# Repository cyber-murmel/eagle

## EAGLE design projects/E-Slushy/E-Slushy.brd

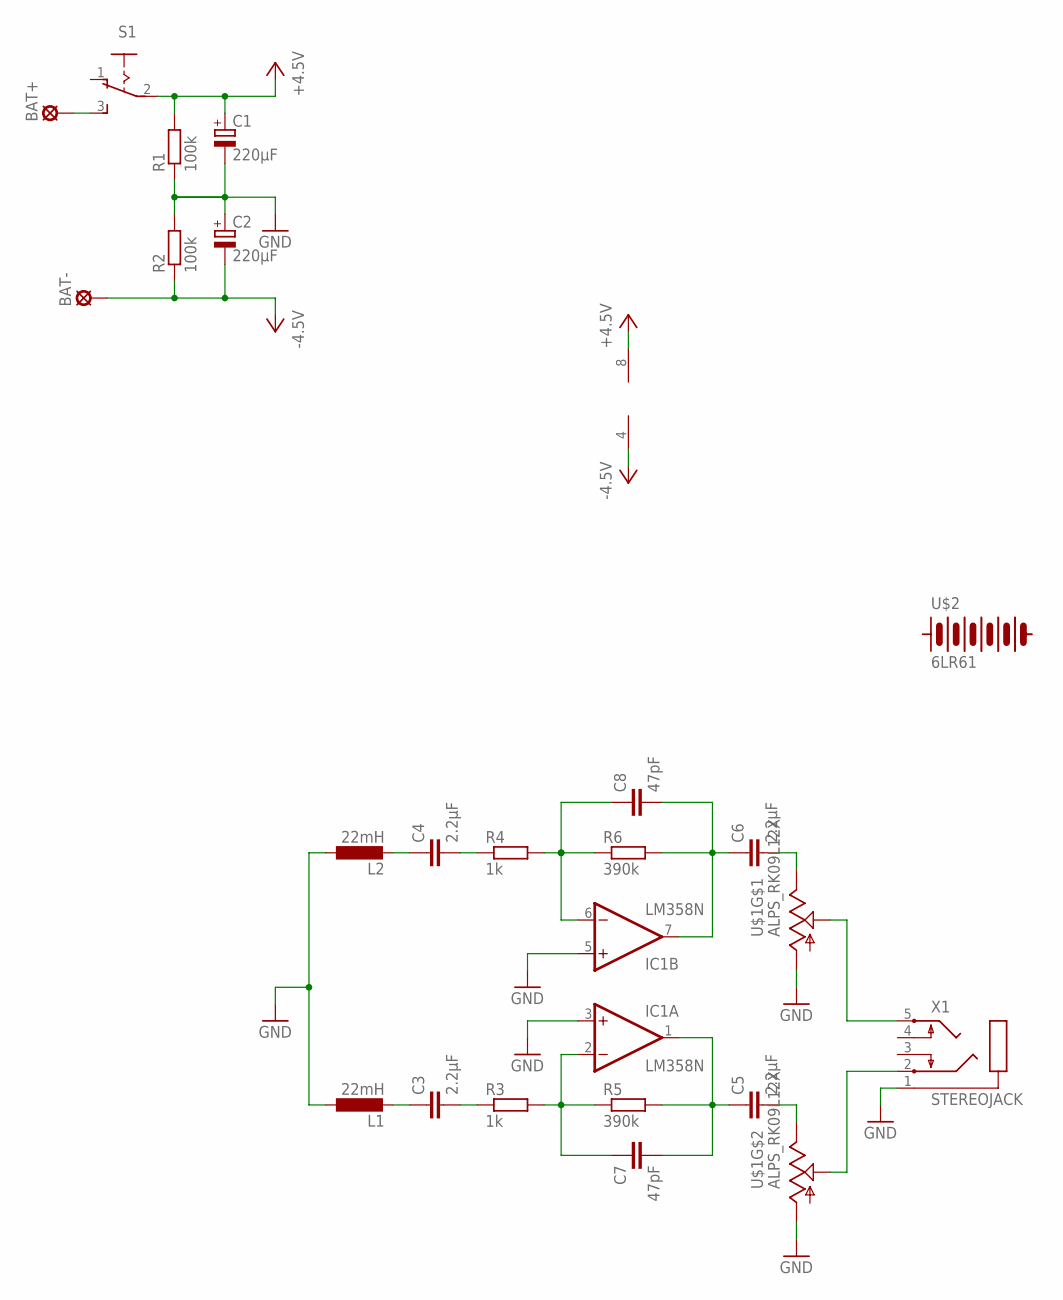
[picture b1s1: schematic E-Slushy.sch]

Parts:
BAT+: SE14
BAT-: SE14
C1, C2: 220μF; PANASONIC_D
C3, C4, C5, C6: 2.2μF; C1206K
C7, C8: 47pF; C1206K
IC1: LM358N; DIL08
L1, L2: 22mH; 6000-XXXX-RC
R1, R2: 100k; R1206
R3, R4: 1k; R1206
R5, R6: 390k; R1206
S1: 255SB
U$1: ALPS_RK09L12X; RK09L12
U$2: 6LR61
X1: STEREOJACK; STX3100

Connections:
+4.5V: C1.+, IC1.8 (V+), R1.2, S1.2
-4.5V: BAT-.MP, C2.-, IC1.4 (V-), R2.1
GND: C1.-, C2.+, IC1.3 (+IN), IC1.5 (+IN), L1.1, L2.1, R1.1, R2.2, U$1.A1 (1), U$1.B1 (1), X1.1
unnamed: C3.1, L1.2
unnamed: C3.2, R3.1
unnamed: C4.1, L2.2
unnamed: C4.2, R4.1
unnamed: C7.1, IC1.2 (-IN), R3.2, R5.1
unnamed: C5.1, C7.2, IC1.1 (OUT), R5.2
unnamed: C8.1, IC1.6 (-IN), R4.2, R6.1
unnamed: C6.1, C8.2, IC1.7 (OUT), R6.2
unnamed: C5.2, U$1.B3 (3)
unnamed: C6.2, U$1.A3 (3)
unnamed: U$1.B2 (2), X1.2
unnamed: U$1.A2 (2), X1.5
unnamed: BAT+.MP, S1.3 (S)

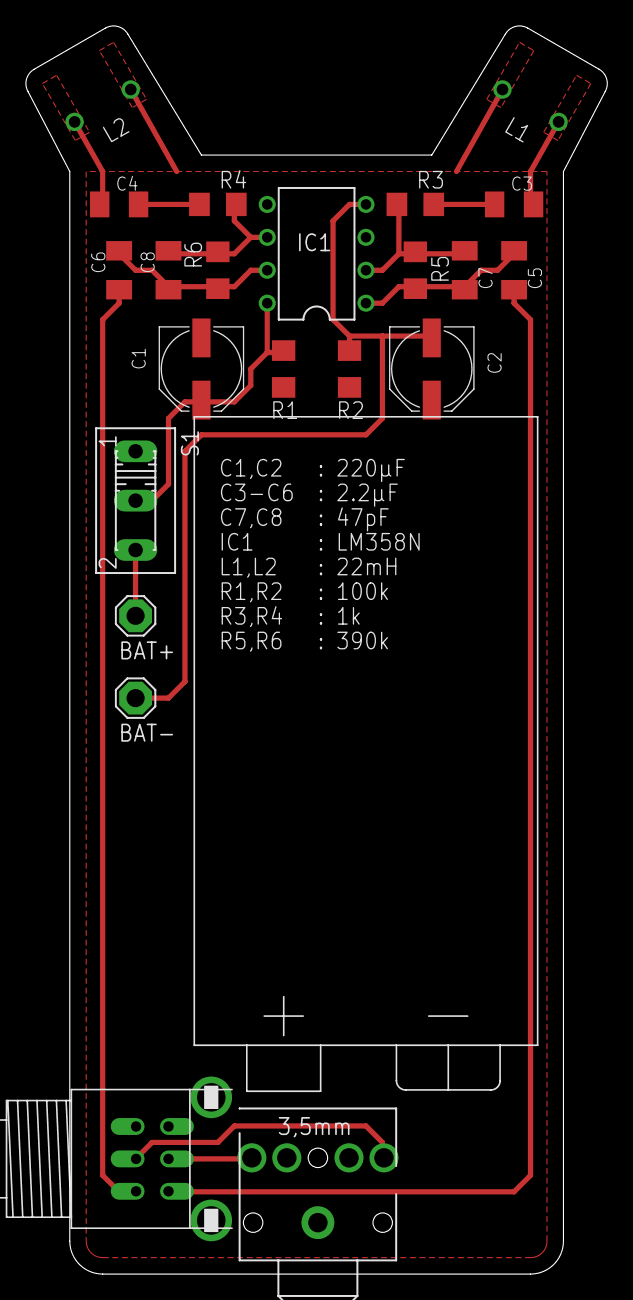
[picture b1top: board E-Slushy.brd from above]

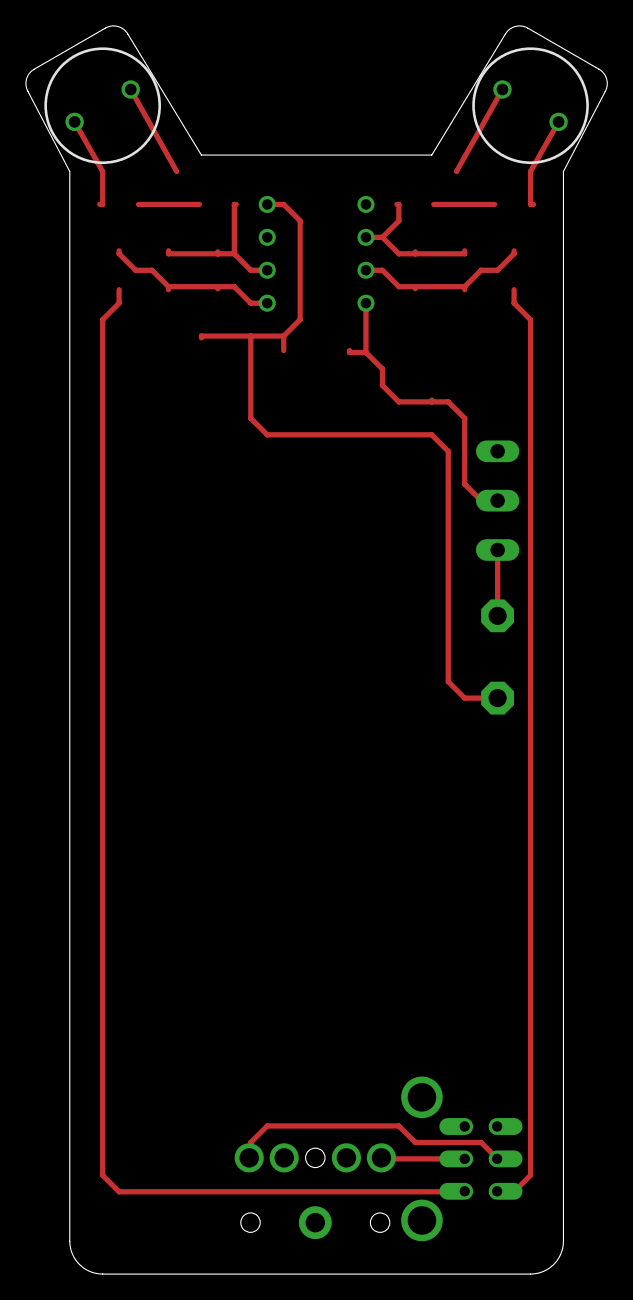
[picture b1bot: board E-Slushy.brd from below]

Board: 2 copper layers, 44.9 x 96.3 mm, 23 parts (2 on the bottom side), 16 nets.

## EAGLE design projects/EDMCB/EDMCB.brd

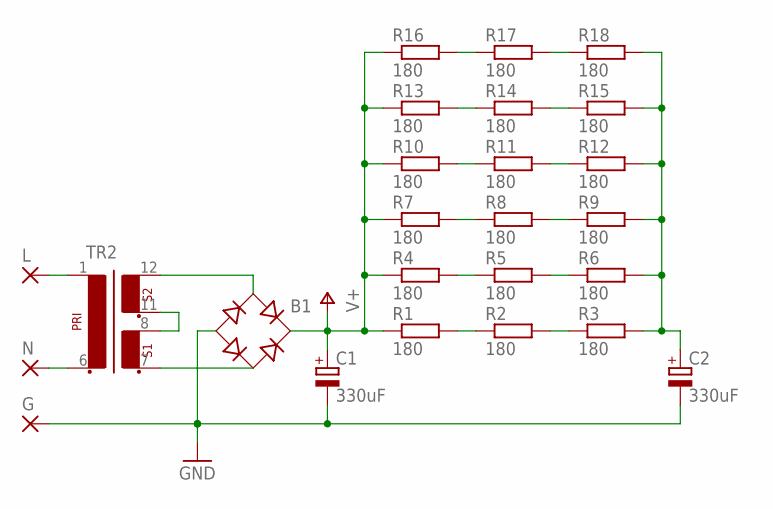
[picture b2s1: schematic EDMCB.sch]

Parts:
B1: RECTIFIER-FB32; FB32
C1, C2: 330uF; SANYO-OSCON_H
G: WIREPAD4,16O1,6; 4,16O1,6
L: WIREPAD4,16O1,6; 4,16O1,6
N: WIREPAD4,16O1,6; 4,16O1,6
R1, R2, R3, R4, R5, R6, R7, R8, R9, R10, R11, R12, R13, R14, R15, R16, R17, R18: 180; VTA52
TR2: EI48-2

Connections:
GND: B1.-, C1.-, C2.-, G.1
unnamed: C2.+, R3.2, R6.2, R9.2, R12.2, R15.2, R18.2
unnamed: R1.2, R2.1
unnamed: R2.2, R3.1
unnamed: N.1, TR2.6 (2)
unnamed: L.1, TR2.1
unnamed: B1.AC1, TR2.12 (6)
unnamed: R4.2, R5.1
unnamed: R5.2, R6.1
unnamed: TR2.8 (4), TR2.11 (5)
unnamed: B1.AC2, TR2.7 (3)
unnamed: R7.2, R8.1
unnamed: R8.2, R9.1
unnamed: R10.2, R11.1
unnamed: R11.2, R12.1
unnamed: R13.2, R14.1
unnamed: R14.2, R15.1
unnamed: R16.2, R17.1
unnamed: R17.2, R18.1
V+: B1.+, C1.+, R1.1, R4.1, R7.1, R10.1, R13.1, R16.1

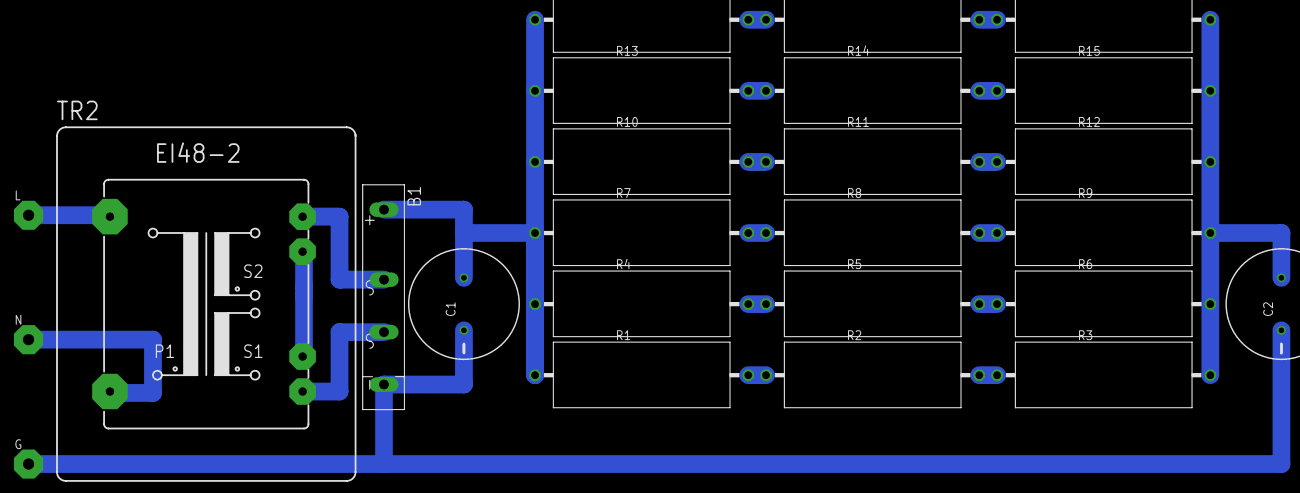
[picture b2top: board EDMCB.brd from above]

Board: 2 copper layers, 25 parts (0 on the bottom side), 20 nets.

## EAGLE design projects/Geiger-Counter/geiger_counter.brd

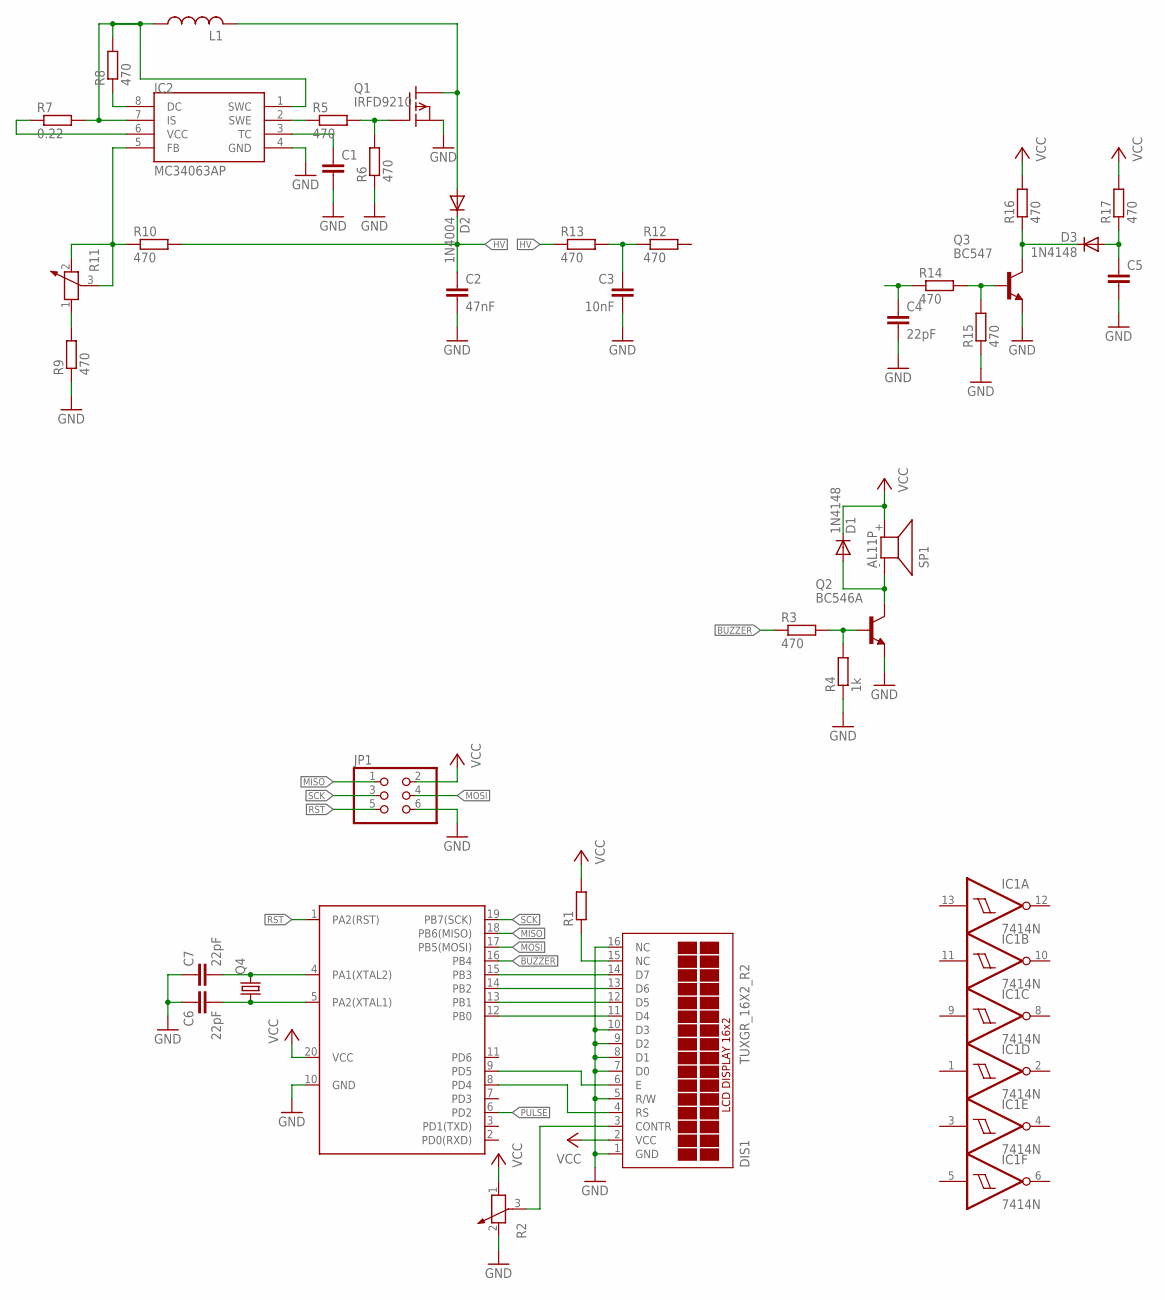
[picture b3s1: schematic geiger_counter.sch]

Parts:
C1, C5: C-EU050-024X044; C050-024X044
C2: 47nF; C075-052X106
C3: 10nF; C075-032X103
C4, C6, C7: 22pF; C050-024X044
D1, D3: 1N4148; DO35-7
D2: 1N4004; DO41-10
DIS1: TUXGR_16X2_R2
IC1: 7414N; DIL14
IC2: MC34063AP; DIL08
JP1: PINHD-2X3; 2X03
L1: L-US6000-XXX-RC; 6000-XXXX-RC
Q1: IRFD9210; DIL04
Q2: BC546A; TO92-EBC
Q3: BC547; TO92-EBC
Q4: CRYSTALHC18U-V; HC18U-V
R1: R-EU_0207/15; 0207/15
R2, R11: POTENTIOMETER_PT-10; PT-10
R3, R5, R6, R8, R9, R10, R12, R13, R14, R15, R16, R17: 470; 0204/7
R4: 1k; 0204/7
R7: 0.22; 0617/17
SP1: AL11P
U$1: TINY2313; DIL20

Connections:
BUZZER: R3.1, U$1.16 (PB4)
GND: C1.2, C2.2, C3.2, C4.2, C5.2, C6.1, C7.1, DIS1.1 (GND), DIS1.5 (R/W), DIS1.7 (D0), DIS1.8 (D1), DIS1.9 (D2), DIS1.10 (D3), DIS1.16 (NC), IC1.7 (GND), IC2.4 (GND), JP1.6, Q1.2 (S), Q2.E, Q3.E, R2.2, R4.1, R6.1, R9.1, R15.1, U$1.10 (GND)
HV: C2.1, D2.C, R10.2, R13.1
MISO: JP1.1, U$1.18 (PB6(MISO))
MOSI: JP1.4, U$1.17 (PB5(MOSI))
unnamed: DIS1.11 (D4), U$1.12 (PB0)
unnamed: DIS1.12 (D5), U$1.13 (PB1)
unnamed: DIS1.13 (D6), U$1.14 (PB2)
unnamed: DIS1.14 (D7), U$1.15 (PB3)
unnamed: DIS1.6 (E), U$1.9 (PD5)
unnamed: DIS1.4 (RS), U$1.8 (PD4)
unnamed: DIS1.15 (NC), R1.1
unnamed: DIS1.3 (CONTR), R2.3
unnamed: IC2.8 (DC), R8.1
unnamed: D1.A, Q2.C, SP1.- (1)
unnamed: IC2.1 (SWC), IC2.7 (IS), L1.1, R7.2, R8.2
unnamed: Q2.B, R3.2, R4.2
unnamed: C1.1, IC2.3 (TC)
unnamed: IC2.2 (SWE), R5.1
unnamed: Q1.1 (G), R5.2, R6.2
unnamed: D2.A, L1.2, Q1.3 (D), Q1.4 (D)
unnamed: IC2.5 (FB), R10.1, R11.2, R11.3
unnamed: Q3.B, R14.2, R15.2
unnamed: IC2.6 (VCC), R7.1
unnamed: R9.2, R11.1
unnamed: C3.1, R12.1, R13.2
unnamed: C4.1, R14.1
unnamed: D3.C, Q3.C, R16.1
unnamed: C5.1, D3.A, R17.1
unnamed: C7.2, Q4.2, U$1.4 (PA1(XTAL2))
unnamed: C6.2, Q4.1, U$1.5 (PA2(XTAL1))
PULSE: U$1.6 (PD2)
RST: JP1.5, U$1.1 (PA2(RST))
SCK: JP1.3, U$1.19 (PB7(SCK))
VCC: D1.C, DIS1.2 (VCC), IC1.14 (VCC), JP1.2, R1.2, R2.1, R16.2, R17.2, SP1.+ (2), U$1.20 (VCC)

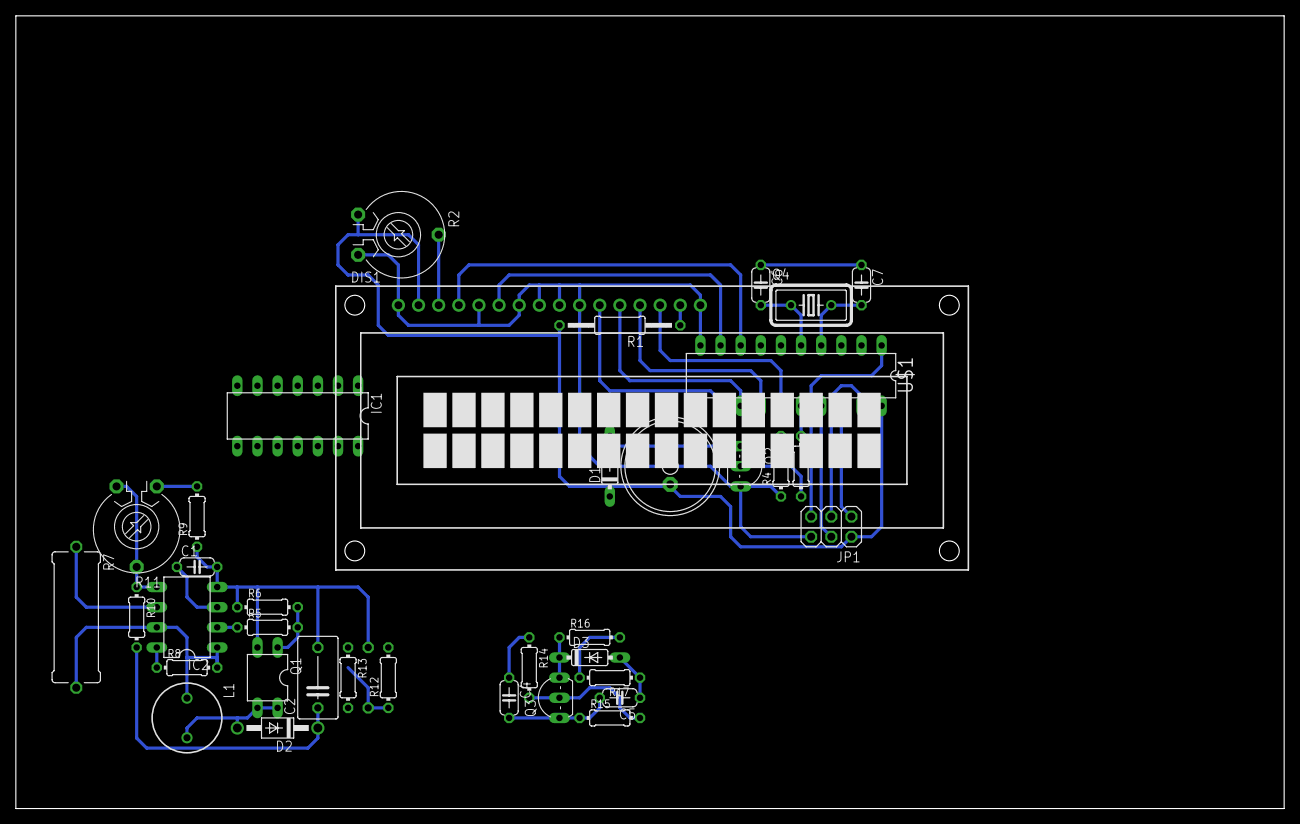
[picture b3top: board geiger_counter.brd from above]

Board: 2 copper layers, 160.0 x 100.0 mm, 38 parts (1 on the bottom side), 34 nets.

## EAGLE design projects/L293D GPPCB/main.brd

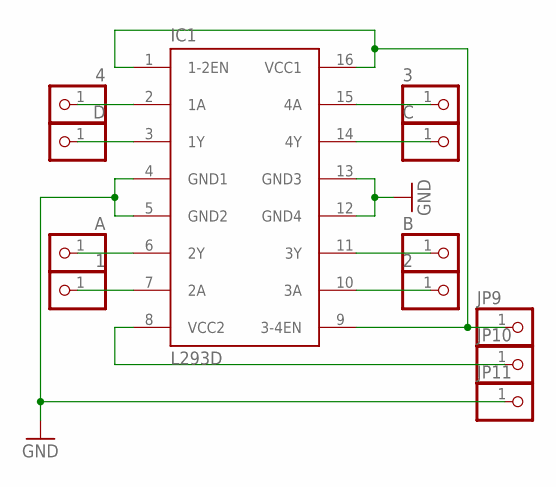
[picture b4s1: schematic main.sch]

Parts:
1, 2, 3, 4: PINHD-1X1; 1X01
A: PINHD-1X1; 1X01
B: PINHD-1X1; 1X01
C: PINHD-1X1; 1X01
D: PINHD-1X1; 1X01
IC1: L293D; DIL16
JP9, JP10, JP11: PINHD-1X1; 1X01

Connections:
GND: IC1.4 (GND1), IC1.5 (GND2), IC1.12 (GND4), IC1.13 (GND3), JP11.1
unnamed: IC1.1 (1-2EN), IC1.9 (3-4EN), IC1.16 (VCC1), JP9.1
unnamed: IC1.8 (VCC2), JP10.1
unnamed: 1.1, IC1.7 (2A)
unnamed: A.1, IC1.6 (2Y)
unnamed: D.1, IC1.3 (1Y)
unnamed: 4.1, IC1.2 (1A)
unnamed: 3.1, IC1.15 (4A)
unnamed: C.1, IC1.14 (4Y)
unnamed: B.1, IC1.11 (3Y)
unnamed: 2.1, IC1.10 (3A)

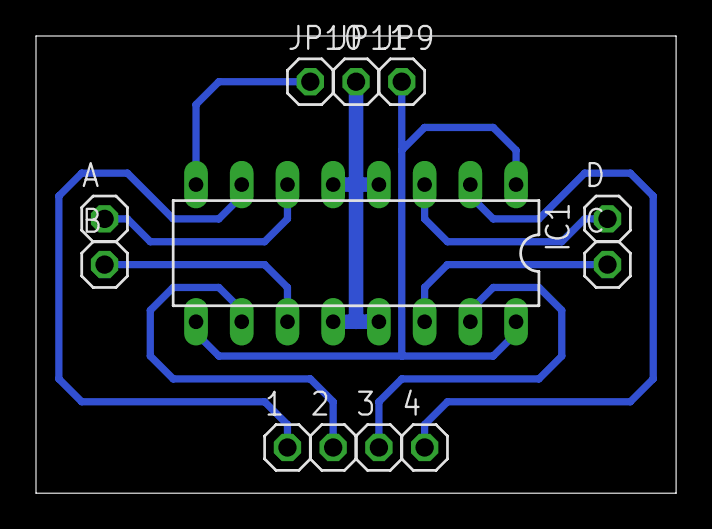
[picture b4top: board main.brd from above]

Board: 2 copper layers, 35.6 x 25.4 mm, 12 parts (0 on the bottom side), 11 nets.

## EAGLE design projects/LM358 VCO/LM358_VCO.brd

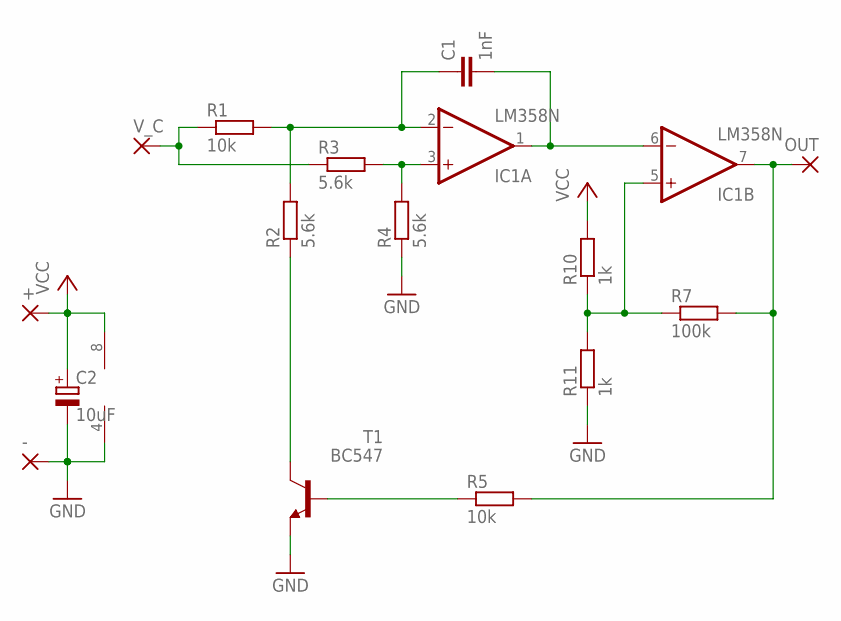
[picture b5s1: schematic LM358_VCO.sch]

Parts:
+: 1,6/0,8
-: 1,6/0,8
C1: 1nF; C050-025X075
C2: 10uF; B45181A
IC1: LM358N; DIL08
OUT: 1,6/0,8
R1, R5: 10k; 0204/7
R2, R3, R4: 5.6k; 0204/7
R7: 100k; 0204/7
R10, R11: 1k; 0204/7
T1: BC547; TO92-CBE
V_C: 1,6/0,8

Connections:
GND: -.1, C2.-, IC1.4 (V-), R4.1, R11.1, T1.E
unnamed: IC1.3 (+IN), R3.2, R4.2
unnamed: C1.1, IC1.2 (-IN), R1.2, R2.2
unnamed: R1.1, R3.1, V_C.1
unnamed: R2.1, T1.C
unnamed: C1.2, IC1.1 (OUT), IC1.6 (-IN)
unnamed: R5.1, T1.B
unnamed: IC1.7 (OUT), OUT.1, R5.2, R7.2
unnamed: IC1.5 (+IN), R7.1, R10.1, R11.2
VCC: +.1, C2.+, IC1.8 (V+), R10.2

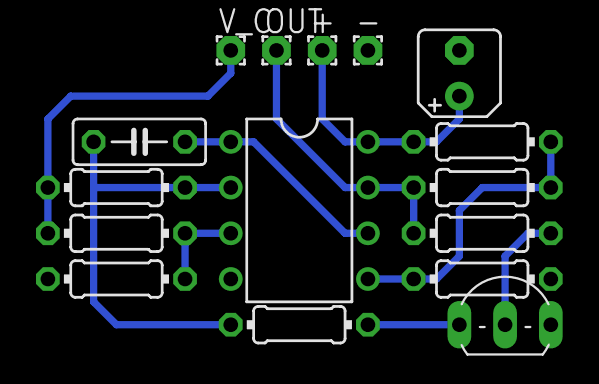
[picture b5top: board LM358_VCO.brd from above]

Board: 2 copper layers, 16 parts (0 on the bottom side), 10 nets.
